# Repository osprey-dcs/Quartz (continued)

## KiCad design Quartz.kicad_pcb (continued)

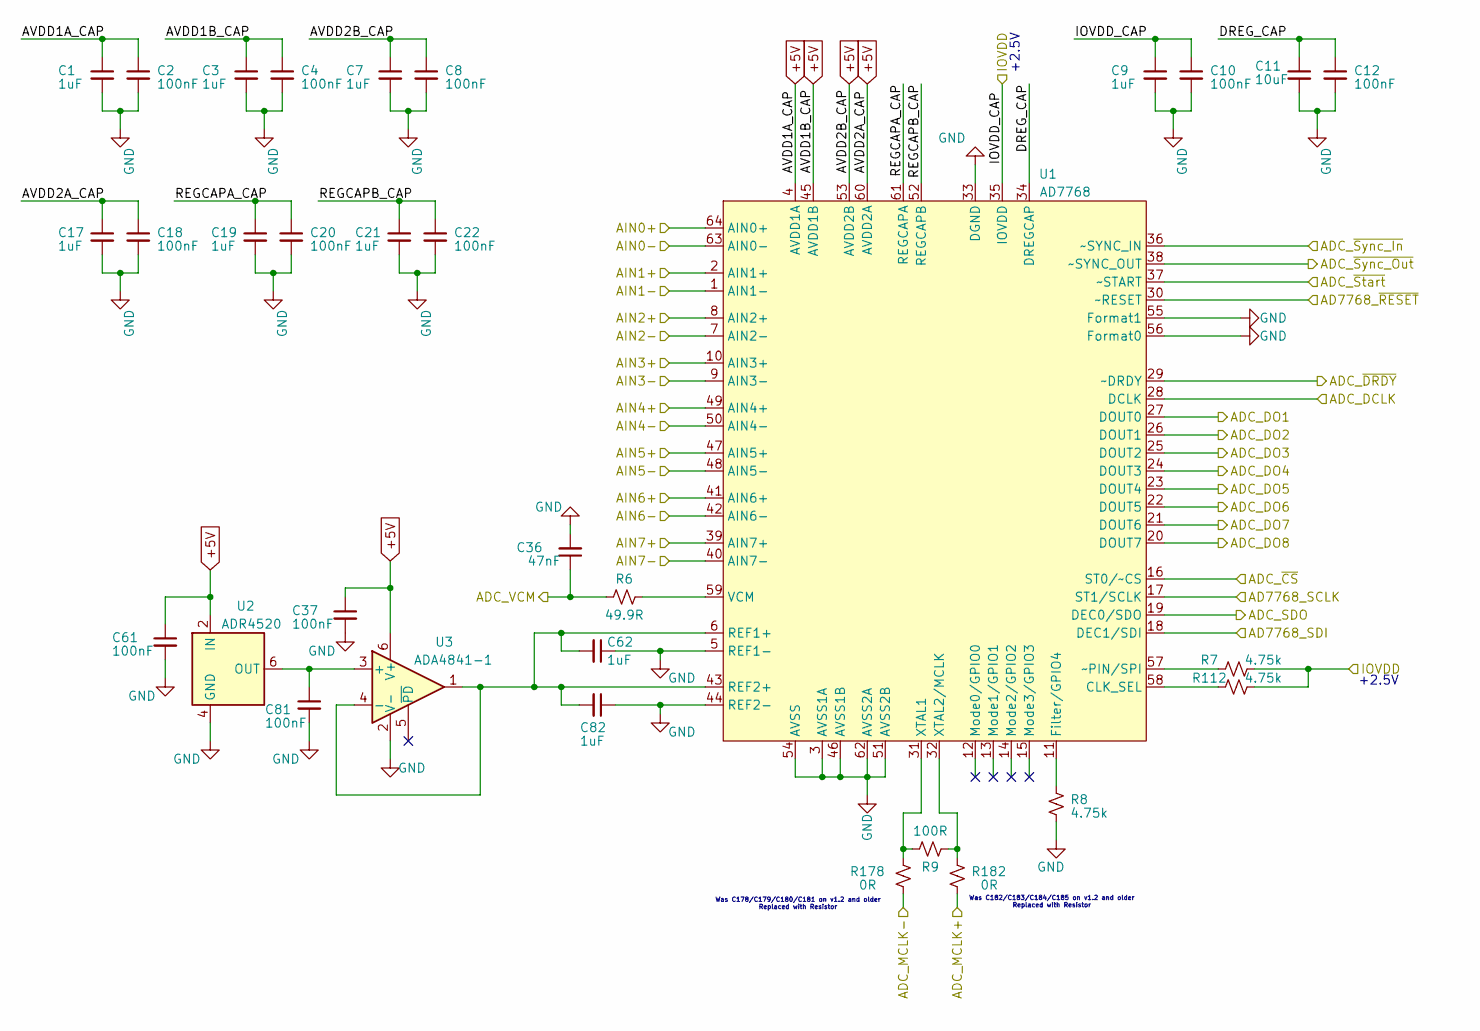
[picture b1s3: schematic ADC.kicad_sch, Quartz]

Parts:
C1, C3, C7, C9, C17, C19, C21, C62, C82: 1uF; C_0402_1005Metric; MPN CL05X105KP5NNNC
C2, C4, C8, C10, C12, C18, C20, C22, C37, C61, C81: 100nF; C_0402_1005Metric; MPN CL05A104KA5NNNC
C11: 10uF; C_0805_2012Metric; MPN CL21A106KOQNNNE
C36: 47nF; C_0402_1005Metric; MPN CGA2B3X7R1H473K050BB
R6: 49.9R; R_0402_1005Metric; MPN RC0402FR-0749R9L
R7, R8, R112: 4.75k; R_0402_1005Metric; MPN RC0402FR-074K75L
R9: 100R; R_0402_1005Metric; MPN RC0402FR-07100RL
R178, R182: 0R; R_0603_1608Metric; MPN ERJ-2GE0R00X
U1: AD7768; LQFP-64_10x10mm_P0.5mm; MPN AD7768BSTZ
U2: ADR4520; SOIC-8_3.9x4.9mm_P1.27mm; MPN ADR4520BRZ
U3: ADA4841-1; SOT-23-6; MPN ADA4841-1YRJZ-R2

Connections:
+5V: C1.1, C2.1, C3.1, C4.1, C7.1, C8.1, C17.1, C18.1, C37.1, C61.1, U1.4 (AVDD1A), U1.45 (AVDD1B), U1.53 (AVDD2B), U1.60 (AVDD2A), U2.2 (IN), U3.6 (V+); also elsewhere on the board
/ADC1/AIN0+: U1.64 (AIN0+); also elsewhere on the board
/ADC1/AIN0-: U1.63 (AIN0-); also elsewhere on the board
/ADC1/AIN1+: U1.2 (AIN1+); also elsewhere on the board
/ADC1/AIN1-: U1.1 (AIN1-); also elsewhere on the board
/ADC1/AIN2+: U1.8 (AIN2+); also elsewhere on the board
/ADC1/AIN2-: U1.7 (AIN2-); also elsewhere on the board
/ADC1/AIN3+: U1.10 (AIN3+); also elsewhere on the board
/ADC1/AIN3-: U1.9 (AIN3-); also elsewhere on the board
/ADC1/AIN4+: U1.49 (AIN4+); also elsewhere on the board
/ADC1/AIN4-: U1.50 (AIN4-); also elsewhere on the board
/ADC1/AIN5+: U1.47 (AIN5+); also elsewhere on the board
/ADC1/AIN5-: U1.48 (AIN5-); also elsewhere on the board
/ADC1/AIN6+: U1.41 (AIN6+); also elsewhere on the board
/ADC1/AIN6-: U1.42 (AIN6-); also elsewhere on the board
/ADC1/AIN7+: U1.39 (AIN7+); also elsewhere on the board
/ADC1/AIN7-: U1.40 (AIN7-); also elsewhere on the board
/ADC1/DREG_CAP: C11.1, C12.1, U1.34 (DREGCAP)
/ADC1/REGCAPA_CAP: C19.1, C20.1, U1.61 (REGCAPA)
/ADC1/REGCAPB_CAP: C21.1, C22.1, U1.52 (REGCAPB)
/ADC_VCM1: C36.1, R6.1; also elsewhere on the board
AD7768_SCLK: U1.17 (ST1/SCLK); also elsewhere on the board
AD7768_SDI: U1.18 (DEC1/SDI); also elsewhere on the board
AD7768_SYNC: U1.36 (~SYNC_IN), U1.38 (~SYNC_OUT); also elsewhere on the board
AD7768_~RESET: U1.30 (~RESET); also elsewhere on the board
AD7768_~Start: U1.37 (~START); also elsewhere on the board
ADC1_DCLK: U1.28 (DCLK); also elsewhere on the board
ADC1_DO1: U1.27 (DOUT0); also elsewhere on the board
ADC1_DO2: U1.26 (DOUT1); also elsewhere on the board
ADC1_DO3: U1.25 (DOUT2); also elsewhere on the board
ADC1_DO4: U1.24 (DOUT3); also elsewhere on the board
ADC1_DO5: U1.23 (DOUT4); also elsewhere on the board
ADC1_DO6: U1.22 (DOUT5); also elsewhere on the board
ADC1_DO7: U1.21 (DOUT6); also elsewhere on the board
ADC1_DO8: U1.20 (DOUT7); also elsewhere on the board
ADC1_MCLK+: R182.2; also elsewhere on the board
ADC1_MCLK-: R178.2; also elsewhere on the board
ADC1_SDO: U1.19 (DEC0/SDO); also elsewhere on the board
ADC1_~CS: U1.16 (ST0/~CS); also elsewhere on the board
ADC1_~DRDY: U1.29 (~DRDY); also elsewhere on the board
GND: C1.2, C2.2, C3.2, C4.2, C7.2, C8.2, C9.2, C10.2, C11.2, C12.2, C17.2, C18.2, C19.2, C20.2, C21.2, C22.2, C36.2, C37.2, C61.2, C62.1, C81.2, C82.1, R8.2, U1.3 (AVSS1A), U1.5 (REF1-), U1.33 (DGND), U1.44 (REF2-), U1.46 (AVSS1B), U1.51 (AVSS2B), U1.54 (AVSS), U1.55 (Format1), U1.56 (Format0), U1.62 (AVSS2A), U2.4 (GND), U3.2 (V-); also elsewhere on the board
unnamed: R112.2, U1.58 (CLK_SEL)
unnamed: R8.1, U1.11 (Filter/GPIO4)
unnamed: C62.2, C82.2, U1.6 (REF1+), U1.43 (REF2+), U3.1, U3.4 (-)
unnamed: R6.2, U1.59 (VCM)
unnamed: R9.1, R178.1, U1.31 (XTAL1)
unnamed: R9.2, R182.1, U1.32 (XTAL2/MCLK)
unnamed: R7.2, U1.57 (~PIN/SPI)
unnamed: C81.1, U2.6 (OUT), U3.3 (+)
P1_2P5V: C9.1, C10.1, R7.1, R112.1, U1.35 (IOVDD); also elsewhere on the board

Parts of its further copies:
C5, C13, C15, C23, C24, C27, C29, C31, C34, C38, C40, C42, C47, C50, C53, C55, C57, C59, C63, C68, C71, C73, C75, C77, C79, C86, C88: 1uF; C_0402_1005Metric; MPN CL05X105KP5NNNC
C6, C14, C16, C25, C26, C28, C30, C33, C35, C39, C41, C43, C45, C46, C48, C49, C52, C54, C56, C58, C60, C64, C66, C67, C70, C72, C74, C76, C78, C80, C84, C85, C87: 100nF; C_0402_1005Metric; MPN CL05A104KA5NNNC
C32, C51, C69: 10uF; C_0805_2012Metric; MPN CL21A106KOQNNNE
C44, C65, C83: 47nF; C_0402_1005Metric; MPN CGA2B3X7R1H473K050BB
R12, R18, R24: 49.9R; R_0402_1005Metric; MPN RC0402FR-0749R9L
R13, R14, R19, R20, R25, R26, R113, R114, R115: 4.75k; R_0402_1005Metric; MPN RC0402FR-074K75L
R15, R21, R27: 100R; R_0402_1005Metric; MPN RC0402FR-07100RL
R179, R180, R181, R183, R184, R185: 0R; R_0603_1608Metric; MPN ERJ-2GE0R00X
U4, U7, U10: AD7768; LQFP-64_10x10mm_P0.5mm; MPN AD7768BSTZ
U5, U8, U11: ADR4520; SOIC-8_3.9x4.9mm_P1.27mm; MPN ADR4520BRZ
U6, U9, U12: ADA4841-1; SOT-23-6; MPN ADA4841-1YRJZ-R2

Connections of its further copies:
+5V: C5.1, C6.1, C13.1, C14.1, C15.1, C16.1, C23.1, C24.1, C25.1, C26.1, C27.1, C28.1, C31.1, C34.1, C35.1, C38.1, C39.1, C45.1, C46.1, C49.1, C53.1, C54.1, C55.1, C56.1, C66.1, C67.1, C71.1, C72.1, C84.1, C85.1, U4.4 (AVDD1A), U4.45 (AVDD1B), U4.53 (AVDD2B), U4.60 (AVDD2A), U5.2 (IN), U6.6 (V+), U7.4 (AVDD1A), U7.45 (AVDD1B), U7.53 (AVDD2B), U7.60 (AVDD2A), U8.2 (IN), U9.6 (V+), U10.4 (AVDD1A), U10.45 (AVDD1B), U10.53 (AVDD2B), U10.60 (AVDD2A), U11.2 (IN), U12.6 (V+); also elsewhere on the board
/ADC2/ADC_~Start: U4.37 (~START); also elsewhere on the board
/ADC2/ADC_~Sync_Out: U4.38 (~SYNC_OUT)
/ADC2/AIN0+: U4.64 (AIN0+); also elsewhere on the board
/ADC2/AIN0-: U4.63 (AIN0-); also elsewhere on the board
/ADC2/AIN1+: U4.2 (AIN1+); also elsewhere on the board
/ADC2/AIN1-: U4.1 (AIN1-); also elsewhere on the board
/ADC2/AIN2+: U4.8 (AIN2+); also elsewhere on the board
/ADC2/AIN2-: U4.7 (AIN2-); also elsewhere on the board
/ADC2/AIN3+: U4.10 (AIN3+); also elsewhere on the board
/ADC2/AIN3-: U4.9 (AIN3-); also elsewhere on the board
/ADC2/AIN4+: U4.49 (AIN4+); also elsewhere on the board
/ADC2/AIN4-: U4.50 (AIN4-); also elsewhere on the board
/ADC2/AIN5+: U4.47 (AIN5+); also elsewhere on the board
/ADC2/AIN5-: U4.48 (AIN5-); also elsewhere on the board
/ADC2/AIN6+: U4.41 (AIN6+); also elsewhere on the board
/ADC2/AIN6-: U4.42 (AIN6-); also elsewhere on the board
/ADC2/AIN7+: U4.39 (AIN7+); also elsewhere on the board
/ADC2/AIN7-: U4.40 (AIN7-); also elsewhere on the board
/ADC2/DREG_CAP: C32.1, C33.1, U4.34 (DREGCAP)
/ADC2/REGCAPA_CAP: C40.1, C41.1, U4.61 (REGCAPA)
/ADC2/REGCAPB_CAP: C42.1, C43.1, U4.52 (REGCAPB)
/ADC3/ADC_~Start: U7.37 (~START); also elsewhere on the board
/ADC3/ADC_~Sync_Out: U7.38 (~SYNC_OUT)
/ADC3/AIN0+: U7.64 (AIN0+); also elsewhere on the board
/ADC3/AIN0-: U7.63 (AIN0-); also elsewhere on the board
/ADC3/AIN1+: U7.2 (AIN1+); also elsewhere on the board
/ADC3/AIN1-: U7.1 (AIN1-); also elsewhere on the board
/ADC3/AIN2+: U7.8 (AIN2+); also elsewhere on the board
/ADC3/AIN2-: U7.7 (AIN2-); also elsewhere on the board
/ADC3/AIN3+: U7.10 (AIN3+); also elsewhere on the board
/ADC3/AIN3-: U7.9 (AIN3-); also elsewhere on the board
/ADC3/AIN4+: U7.49 (AIN4+); also elsewhere on the board
/ADC3/AIN4-: U7.50 (AIN4-); also elsewhere on the board
/ADC3/AIN5+: U7.47 (AIN5+); also elsewhere on the board
/ADC3/AIN5-: U7.48 (AIN5-); also elsewhere on the board
/ADC3/AIN6+: U7.41 (AIN6+); also elsewhere on the board
/ADC3/AIN6-: U7.42 (AIN6-); also elsewhere on the board
/ADC3/AIN7+: U7.39 (AIN7+); also elsewhere on the board
/ADC3/AIN7-: U7.40 (AIN7-); also elsewhere on the board
/ADC3/DREG_CAP: C51.1, C52.1, U7.34 (DREGCAP)
/ADC3/REGCAPA_CAP: C57.1, C58.1, U7.61 (REGCAPA)
/ADC3/REGCAPB_CAP: C63.1, C64.1, U7.52 (REGCAPB)
/ADC4/ADC_~Start: U10.37 (~START); also elsewhere on the board
/ADC4/ADC_~Sync_Out: U10.38 (~SYNC_OUT)
/ADC4/AIN0+: U10.64 (AIN0+); also elsewhere on the board
/ADC4/AIN0-: U10.63 (AIN0-); also elsewhere on the board
/ADC4/AIN1+: U10.2 (AIN1+); also elsewhere on the board
/ADC4/AIN1-: U10.1 (AIN1-); also elsewhere on the board
/ADC4/AIN2+: U10.8 (AIN2+); also elsewhere on the board
/ADC4/AIN2-: U10.7 (AIN2-); also elsewhere on the board
/ADC4/AIN3+: U10.10 (AIN3+); also elsewhere on the board
/ADC4/AIN3-: U10.9 (AIN3-); also elsewhere on the board
/ADC4/AIN4+: U10.49 (AIN4+); also elsewhere on the board
/ADC4/AIN4-: U10.50 (AIN4-); also elsewhere on the board
/ADC4/AIN5+: U10.47 (AIN5+); also elsewhere on the board
/ADC4/AIN5-: U10.48 (AIN5-); also elsewhere on the board
/ADC4/AIN6+: U10.41 (AIN6+); also elsewhere on the board
/ADC4/AIN6-: U10.42 (AIN6-); also elsewhere on the board
/ADC4/AIN7+: U10.39 (AIN7+); also elsewhere on the board
/ADC4/AIN7-: U10.40 (AIN7-); also elsewhere on the board
/ADC4/DREG_CAP: C69.1, C70.1, U10.34 (DREGCAP)
/ADC4/REGCAPA_CAP: C73.1, C78.1, U10.61 (REGCAPA)
/ADC4/REGCAPB_CAP: C79.1, C80.1, U10.52 (REGCAPB)
/ADC_VCM2: C44.1, R12.1; also elsewhere on the board
/ADC_VCM3: C65.1, R18.1; also elsewhere on the board
/ADC_VCM4: C83.1, R24.1; also elsewhere on the board
AD7768_SCLK: U4.17 (ST1/SCLK), U7.17 (ST1/SCLK), U10.17 (ST1/SCLK); also elsewhere on the board
AD7768_SDI: U4.18 (DEC1/SDI), U7.18 (DEC1/SDI), U10.18 (DEC1/SDI); also elsewhere on the board
AD7768_SYNC: U4.36 (~SYNC_IN), U7.36 (~SYNC_IN), U10.36 (~SYNC_IN); also elsewhere on the board
AD7768_~RESET: U4.30 (~RESET), U7.30 (~RESET), U10.30 (~RESET); also elsewhere on the board
ADC2_DCLK: U4.28 (DCLK); also elsewhere on the board
ADC2_DO1: U4.27 (DOUT0); also elsewhere on the board
ADC2_DO2: U4.26 (DOUT1); also elsewhere on the board
ADC2_DO3: U4.25 (DOUT2); also elsewhere on the board
ADC2_DO4: U4.24 (DOUT3); also elsewhere on the board
ADC2_DO5: U4.23 (DOUT4); also elsewhere on the board
ADC2_DO6: U4.22 (DOUT5); also elsewhere on the board
ADC2_DO7: U4.21 (DOUT6); also elsewhere on the board
ADC2_DO8: U4.20 (DOUT7); also elsewhere on the board
ADC2_MCLK+: R183.2; also elsewhere on the board
ADC2_MCLK-: R179.2; also elsewhere on the board
ADC2_SDO: U4.19 (DEC0/SDO); also elsewhere on the board
ADC2_~CS: U4.16 (ST0/~CS); also elsewhere on the board
ADC2_~DRDY: U4.29 (~DRDY); also elsewhere on the board
ADC3_DCLK: U7.28 (DCLK); also elsewhere on the board
ADC3_DO1: U7.27 (DOUT0); also elsewhere on the board
ADC3_DO2: U7.26 (DOUT1); also elsewhere on the board
ADC3_DO3: U7.25 (DOUT2); also elsewhere on the board
ADC3_DO4: U7.24 (DOUT3); also elsewhere on the board
ADC3_DO5: U7.23 (DOUT4); also elsewhere on the board
ADC3_DO6: U7.22 (DOUT5); also elsewhere on the board
ADC3_DO7: U7.21 (DOUT6); also elsewhere on the board
ADC3_DO8: U7.20 (DOUT7); also elsewhere on the board
ADC3_MCLK+: R184.2; also elsewhere on the board
ADC3_MCLK-: R180.2; also elsewhere on the board
ADC3_SDO: U7.19 (DEC0/SDO); also elsewhere on the board
ADC3_~CS: U7.16 (ST0/~CS); also elsewhere on the board
ADC3_~DRDY: U7.29 (~DRDY); also elsewhere on the board
ADC4_DCLK: U10.28 (DCLK); also elsewhere on the board
ADC4_DO1: U10.27 (DOUT0); also elsewhere on the board
ADC4_DO2: U10.26 (DOUT1); also elsewhere on the board
ADC4_DO3: U10.25 (DOUT2); also elsewhere on the board
ADC4_DO4: U10.24 (DOUT3); also elsewhere on the board
ADC4_DO5: U10.23 (DOUT4); also elsewhere on the board
ADC4_DO6: U10.22 (DOUT5); also elsewhere on the board
ADC4_DO7: U10.21 (DOUT6); also elsewhere on the board
ADC4_DO8: U10.20 (DOUT7); also elsewhere on the board
ADC4_MCLK+: R185.2; also elsewhere on the board
ADC4_MCLK-: R181.2; also elsewhere on the board
ADC4_SDO: U10.19 (DEC0/SDO); also elsewhere on the board
ADC4_~CS: U10.16 (ST0/~CS); also elsewhere on the board
ADC4_~DRDY: U10.29 (~DRDY); also elsewhere on the board
GND: C5.2, C6.2, C13.2, C14.2, C15.2, C16.2, C23.2, C24.2, C25.2, C26.2, C27.2, C28.2, C29.2, C30.2, C31.2, C32.2, C33.2, C34.2, C35.2, C38.2, C39.2, C40.2, C41.2, C42.2, C43.2, C44.2, C45.2, C46.2, C47.2, C48.2, C49.2, C50.1, C51.2, C52.2, C53.2, C54.2, C55.2, C56.2, C57.2, C58.2, C59.2, C60.2, C63.2, C64.2, C65.2, C66.2, C67.2, C68.1, C69.2, C70.2, C71.2, C72.2, C73.2, C74.2, C75.1, C76.2, C77.1, C78.2, C79.2, C80.2, C83.2, C84.2, C85.2, C86.1, C87.2, C88.1, R14.2, R20.2, R26.2, U4.3 (AVSS1A), U4.5 (REF1-), U4.33 (DGND), U4.44 (REF2-), U4.46 (AVSS1B), U4.51 (AVSS2B), U4.54 (AVSS), U4.55 (Format1), U4.56 (Format0), U4.62 (AVSS2A), U5.4 (GND), U6.2 (V-), U7.3 (AVSS1A), U7.5 (REF1-), U7.33 (DGND), U7.44 (REF2-), U7.46 (AVSS1B), U7.51 (AVSS2B), U7.54 (AVSS), U7.55 (Format1), U7.56 (Format0), U7.62 (AVSS2A), U8.4 (GND), U9.2 (V-), U10.3 (AVSS1A), U10.5 (REF1-), U10.33 (DGND), U10.44 (REF2-), U10.46 (AVSS1B), U10.51 (AVSS2B), U10.54 (AVSS), U10.55 (Format1), U10.56 (Format0), U10.62 (AVSS2A), U11.4 (GND), U12.2 (V-); also elsewhere on the board
unnamed: R113.2, U4.58 (CLK_SEL)
unnamed: R14.1, U4.11 (Filter/GPIO4)
unnamed: C50.2, C75.2, U4.6 (REF1+), U4.43 (REF2+), U6.1, U6.4 (-)
unnamed: R12.2, U4.59 (VCM)
unnamed: R15.1, R179.1, U4.31 (XTAL1)
unnamed: R15.2, R183.1, U4.32 (XTAL2/MCLK)
unnamed: R13.2, U4.57 (~PIN/SPI)
unnamed: C74.1, U5.6 (OUT), U6.3 (+)
unnamed: R114.2, U7.58 (CLK_SEL)
unnamed: R20.1, U7.11 (Filter/GPIO4)
unnamed: C68.2, C77.2, U7.6 (REF1+), U7.43 (REF2+), U9.1, U9.4 (-)
unnamed: R18.2, U7.59 (VCM)
unnamed: R21.1, R180.1, U7.31 (XTAL1)
unnamed: R21.2, R184.1, U7.32 (XTAL2/MCLK)
unnamed: R19.2, U7.57 (~PIN/SPI)
unnamed: C76.1, U8.6 (OUT), U9.3 (+)
unnamed: R115.2, U10.58 (CLK_SEL)
unnamed: R26.1, U10.11 (Filter/GPIO4)
unnamed: C86.2, C88.2, U10.6 (REF1+), U10.43 (REF2+), U12.1, U12.4 (-)
unnamed: R24.2, U10.59 (VCM)
unnamed: R27.1, R181.1, U10.31 (XTAL1)
unnamed: R27.2, R185.1, U10.32 (XTAL2/MCLK)
unnamed: R25.2, U10.57 (~PIN/SPI)
unnamed: C87.1, U11.6 (OUT), U12.3 (+)
P1_2P5V: C29.1, C30.1, R13.1, R113.1, U4.35 (IOVDD); also elsewhere on the board
P2_2P5V: C47.1, C48.1, C59.1, C60.1, R19.1, R25.1, R114.1, R115.1, U7.35 (IOVDD), U10.35 (IOVDD); also elsewhere on the board

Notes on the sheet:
+2.5V
Was C178/C179/C180/C181 on v1.2 and older Replaced with Resistor
Was C182/C183/C184/C185 on v1.2 and older Replaced with Resistor

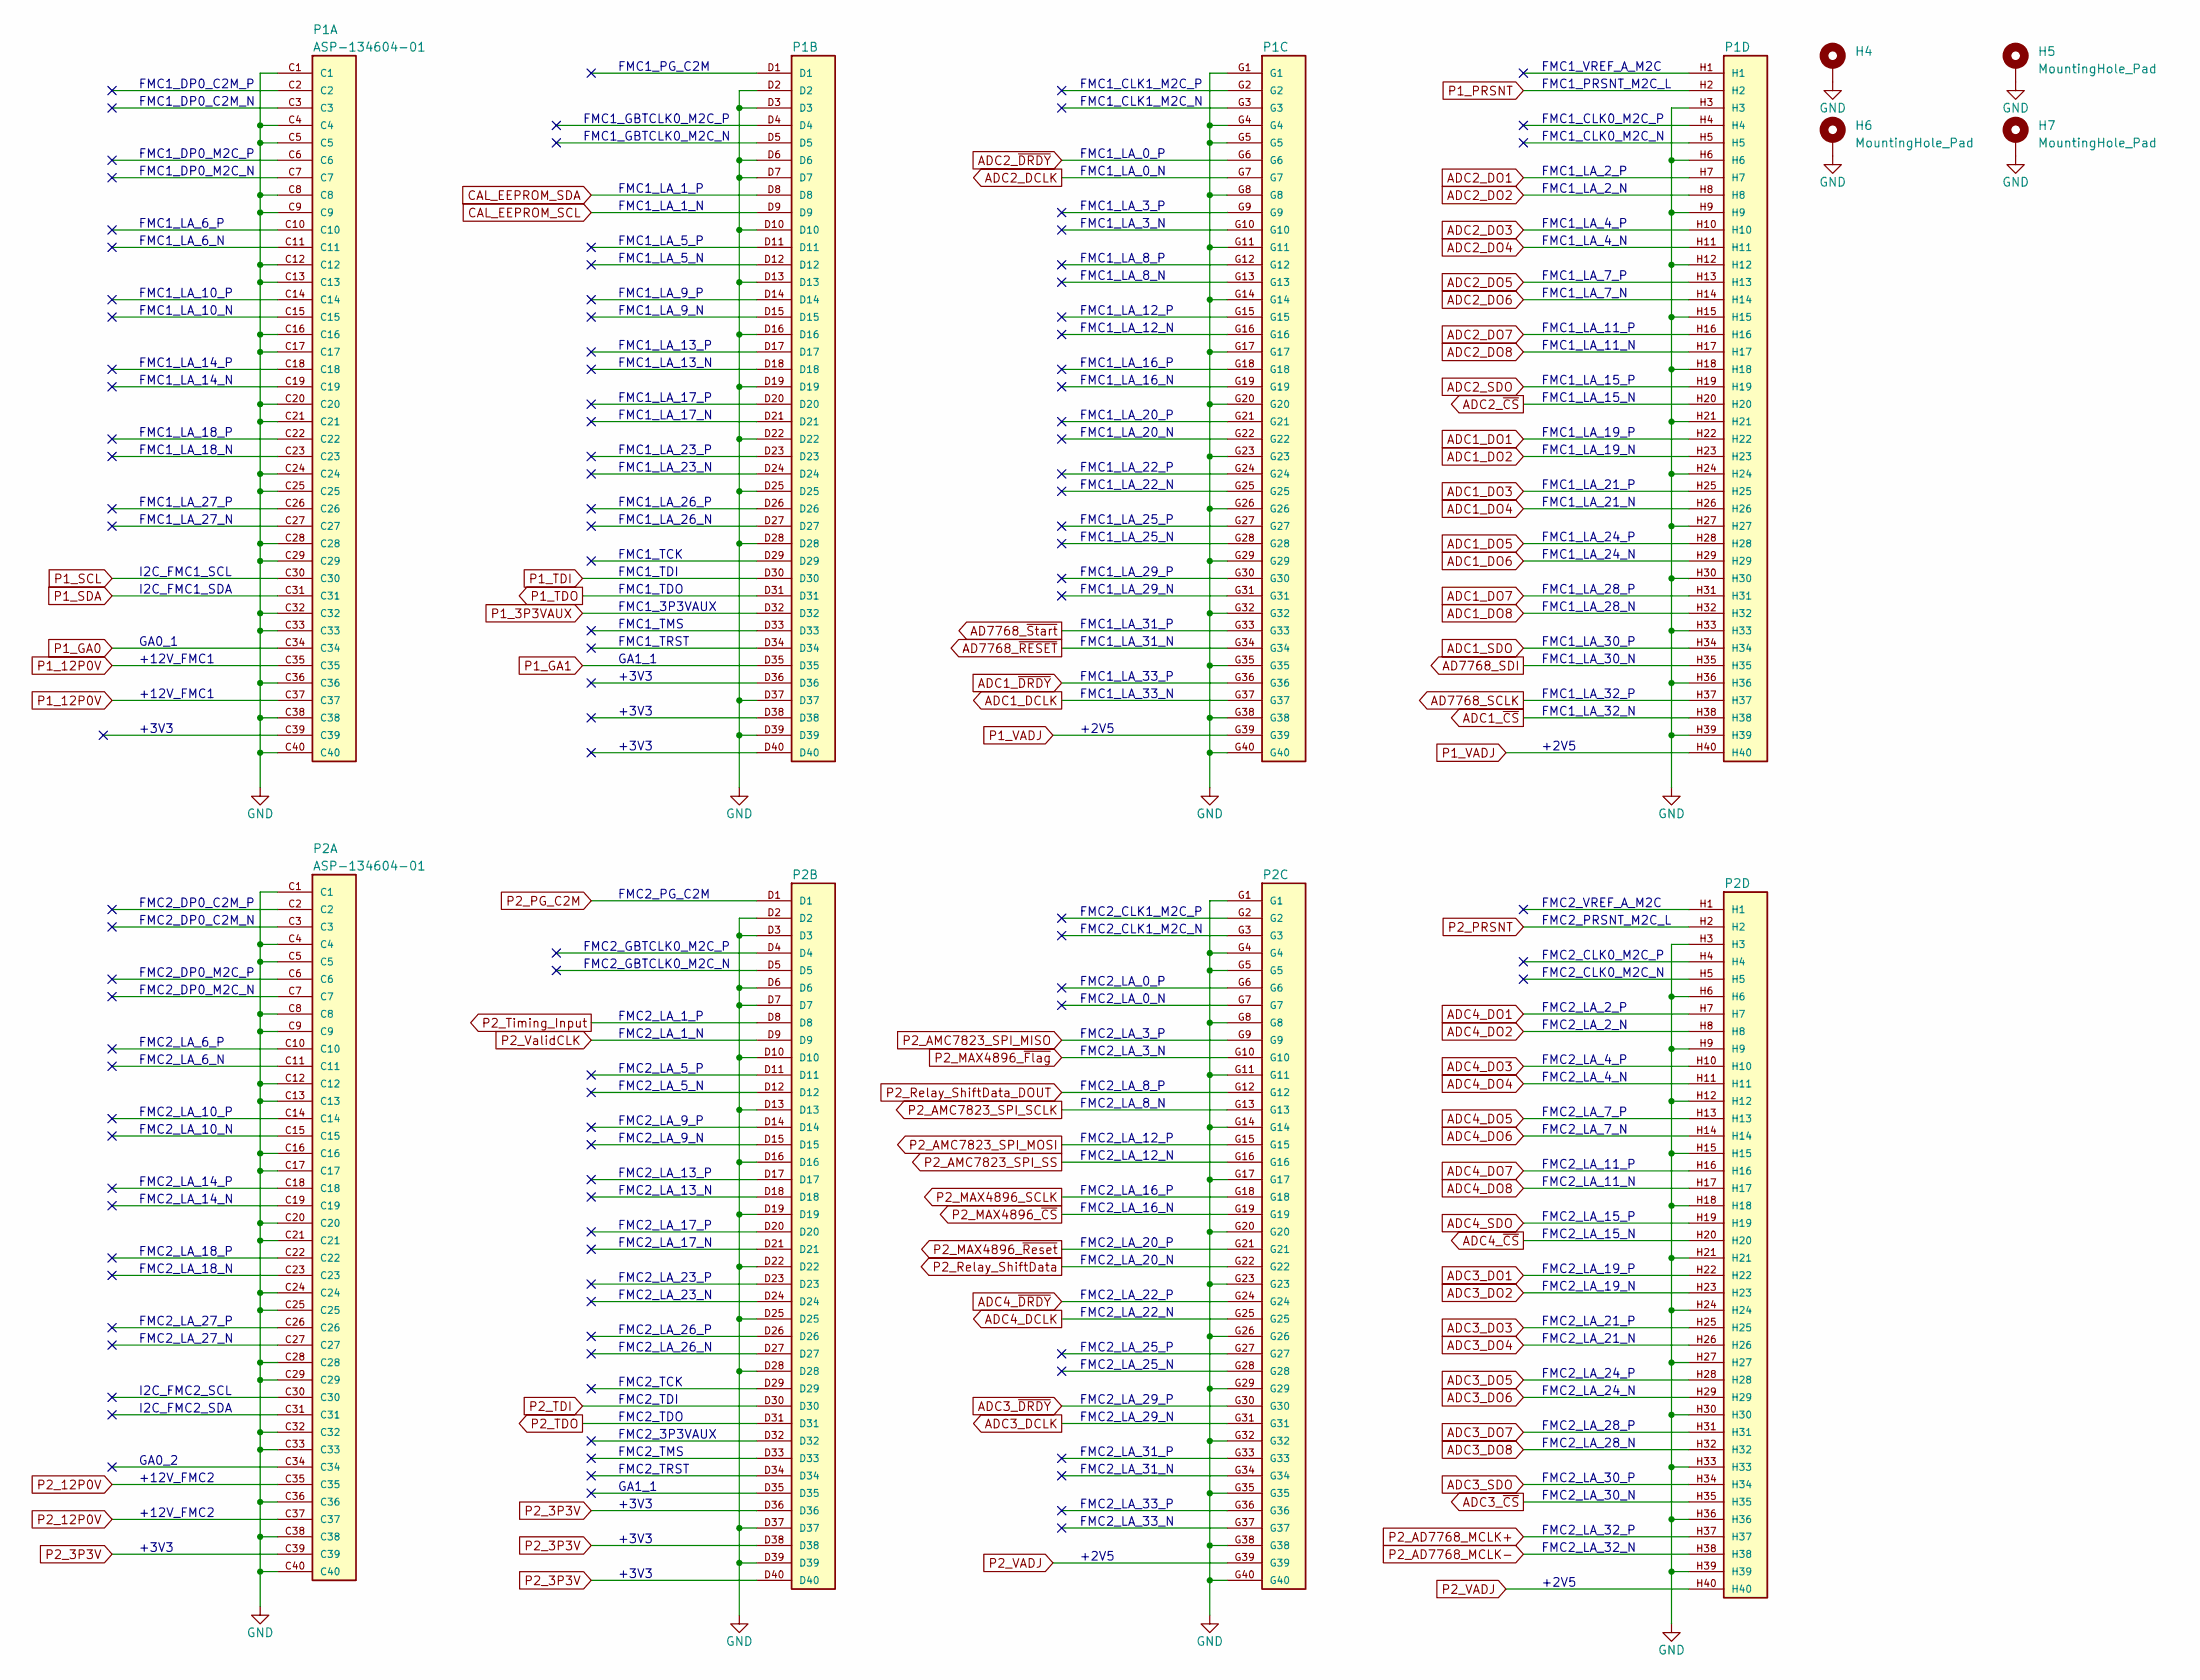
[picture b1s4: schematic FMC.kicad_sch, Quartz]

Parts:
H4, H5, H6, H7: MountingHole_Pad; Mounting Hole 3mm hole 5mm ring
P1, P2: ASP-134604-01; SAMTEC_ASP-134604-01; MPN ASP-134604-01

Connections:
AD7768_SCLK: P1.H37; also elsewhere on the board
AD7768_SDI: P1.H35; also elsewhere on the board
AD7768_~RESET: P1.G34; also elsewhere on the board
AD7768_~Start: P1.G33; also elsewhere on the board
ADC1_DCLK: P1.G37; also elsewhere on the board
ADC1_DO1: P1.H22; also elsewhere on the board
ADC1_DO2: P1.H23; also elsewhere on the board
ADC1_DO3: P1.H25; also elsewhere on the board
ADC1_DO4: P1.H26; also elsewhere on the board
ADC1_DO5: P1.H28; also elsewhere on the board
ADC1_DO6: P1.H29; also elsewhere on the board
ADC1_DO7: P1.H31; also elsewhere on the board
ADC1_DO8: P1.H32; also elsewhere on the board
ADC1_SDO: P1.H34; also elsewhere on the board
ADC1_~CS: P1.H38; also elsewhere on the board
ADC1_~DRDY: P1.G36; also elsewhere on the board
ADC2_DCLK: P1.G7; also elsewhere on the board
ADC2_DO1: P1.H7; also elsewhere on the board
ADC2_DO2: P1.H8; also elsewhere on the board
ADC2_DO3: P1.H10; also elsewhere on the board
ADC2_DO4: P1.H11; also elsewhere on the board
ADC2_DO5: P1.H13; also elsewhere on the board
ADC2_DO6: P1.H14; also elsewhere on the board
ADC2_DO7: P1.H16; also elsewhere on the board
ADC2_DO8: P1.H17; also elsewhere on the board
ADC2_SDO: P1.H19; also elsewhere on the board
ADC2_~CS: P1.H20; also elsewhere on the board
ADC2_~DRDY: P1.G6; also elsewhere on the board
ADC3_DCLK: P2.G31; also elsewhere on the board
ADC3_DO1: P2.H22; also elsewhere on the board
ADC3_DO2: P2.H23; also elsewhere on the board
ADC3_DO3: P2.H25; also elsewhere on the board
ADC3_DO4: P2.H26; also elsewhere on the board
ADC3_DO5: P2.H28; also elsewhere on the board
ADC3_DO6: P2.H29; also elsewhere on the board
ADC3_DO7: P2.H31; also elsewhere on the board
ADC3_DO8: P2.H32; also elsewhere on the board
ADC3_SDO: P2.H34; also elsewhere on the board
ADC3_~CS: P2.H35; also elsewhere on the board
ADC3_~DRDY: P2.G30; also elsewhere on the board
ADC4_DCLK: P2.G25; also elsewhere on the board
ADC4_DO1: P2.H7; also elsewhere on the board
ADC4_DO2: P2.H8; also elsewhere on the board
ADC4_DO3: P2.H10; also elsewhere on the board
ADC4_DO4: P2.H11; also elsewhere on the board
ADC4_DO5: P2.H13; also elsewhere on the board
ADC4_DO6: P2.H14; also elsewhere on the board
ADC4_DO7: P2.H16; also elsewhere on the board
ADC4_DO8: P2.H17; also elsewhere on the board
ADC4_SDO: P2.H19; also elsewhere on the board
ADC4_~CS: P2.H20; also elsewhere on the board
ADC4_~DRDY: P2.G24; also elsewhere on the board
CAL_EEPROM_SCL: P1.D9; also elsewhere on the board
CAL_EEPROM_SDA: P1.D8; also elsewhere on the board
GND: H4.1, H5.1, H6.1, H7.1, P1.C1, P1.C4, P1.C5, P1.C8, P1.C9, P1.C12, P1.C13, P1.C16, P1.C17, P1.C20, P1.C21, P1.C24, P1.C25, P1.C28, P1.C29, P1.C32, P1.C33, P1.C36, P1.C38, P1.C40, P1.D2, P1.D3, P1.D6, P1.D7, P1.D10, P1.D13, P1.D16, P1.D19, P1.D22, P1.D25, P1.D28, P1.D37, P1.D39, P1.G1, P1.G4, P1.G5, P1.G8, P1.G11, P1.G14, P1.G17, P1.G20, P1.G23, P1.G26, P1.G29, P1.G32, P1.G35, P1.G38, P1.G40, P1.H3, P1.H6, P1.H9, P1.H12, P1.H15, P1.H18, P1.H21, P1.H24, P1.H27, P1.H30, P1.H33, P1.H36, P1.H39, P2.C1, P2.C4, P2.C5, P2.C8, P2.C9, P2.C12, P2.C13, P2.C16, P2.C17, P2.C20, P2.C21, P2.C24, P2.C25, P2.C28, P2.C29, P2.C32, P2.C33, P2.C36, P2.C38, P2.C40, P2.D2, P2.D3, P2.D6, P2.D7, P2.D10, P2.D13, P2.D16, P2.D19, P2.D22, P2.D25, P2.D28, P2.D37, P2.D39, P2.G1, P2.G4, P2.G5, P2.G8, P2.G11, P2.G14, P2.G17, P2.G20, P2.G23, P2.G26, P2.G29, P2.G32, P2.G35, P2.G38, P2.G40, P2.H3, P2.H6, P2.H9, P2.H12, P2.H15, P2.H18, P2.H21, P2.H24, P2.H27, P2.H30, P2.H33, P2.H36, P2.H39; also elsewhere on the board
P1_3P3VAUX: P1.D32; also elsewhere on the board
P1_12P0V: P1.C35, P1.C37; also elsewhere on the board
P1_GA0: P1.C34; also elsewhere on the board
P1_GA1: P1.D35; also elsewhere on the board
P1_PRSNT: P1.H2; also elsewhere on the board
P1_SCL: P1.C30; also elsewhere on the board
P1_SDA: P1.C31; also elsewhere on the board
P1_TDI: P1.D30; also elsewhere on the board
P1_TDO: P1.D31; also elsewhere on the board
P1_VADJ: P1.G39, P1.H40; also elsewhere on the board
P2_3P3V: P2.C39, P2.D36, P2.D38, P2.D40; also elsewhere on the board
P2_12P0V: P2.C35, P2.C37; also elsewhere on the board
P2_AD7768_MCLK+: P2.H37; also elsewhere on the board
P2_AD7768_MCLK-: P2.H38; also elsewhere on the board
P2_AMC7823_SPI_MISO: P2.G9; also elsewhere on the board
P2_AMC7823_SPI_MOSI: P2.G15; also elsewhere on the board
P2_AMC7823_SPI_SCLK: P2.G13; also elsewhere on the board
P2_AMC7823_SPI_SS: P2.G16; also elsewhere on the board
P2_MAX4896_SCLK: P2.G18; also elsewhere on the board
P2_MAX4896_~CS: P2.G19; also elsewhere on the board
P2_MAX4896_~Flag: P2.G10; also elsewhere on the board
P2_MAX4896_~Reset: P2.G21; also elsewhere on the board
P2_PG_C2M: P2.D1; also elsewhere on the board
P2_PRSNT: P2.H2; also elsewhere on the board
P2_Relay_ShiftData: P2.G22; also elsewhere on the board
P2_Relay_ShiftData_DOUT: P2.G12; also elsewhere on the board
P2_TDI: P2.D30; also elsewhere on the board
P2_TDO: P2.D31; also elsewhere on the board
P2_Timing_Input: P2.D8; also elsewhere on the board
P2_VADJ: P2.G39, P2.H40; also elsewhere on the board
P2_ValidCLK: P2.D9; also elsewhere on the board

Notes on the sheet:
FMC1_DP0_C2M_N
FMC1_TDO
FMC2_LA_16_P
FMC2_LA_4_N
FMC2_DP0_M2C_P
FMC1_LA_25_P
FMC2_LA_19_N
FMC1_LA_20_P
FMC2_LA_30_P
FMC1_LA_26_N
FMC1_LA_12_P
FMC1_LA_29_N
FMC1_LA_5_P
FMC1_LA_24_P
FMC1_LA_33_N
FMC2_VREF_A_M2C
FMC2_LA_20_P
FMC1_LA_22_N
FMC2_DP0_M2C_N
FMC1_LA_1_P
+2V5
FMC2_LA_15_P
FMC2_LA_25_P
FMC2_LA_18_N
FMC2_LA_17_P
GA0_1
FMC2_LA_19_P
FMC1_LA_11_N
FMC2_LA_5_P
FMC2_LA_29_N
FMC1_LA_0_P
FMC2_LA_31_N
FMC2_LA_23_P
FMC1_LA_16_N
FMC2_LA_10_P
FMC1_LA_3_N
FMC2_LA_26_P
FMC1_LA_26_P
+3V3
FMC2_LA_14_P

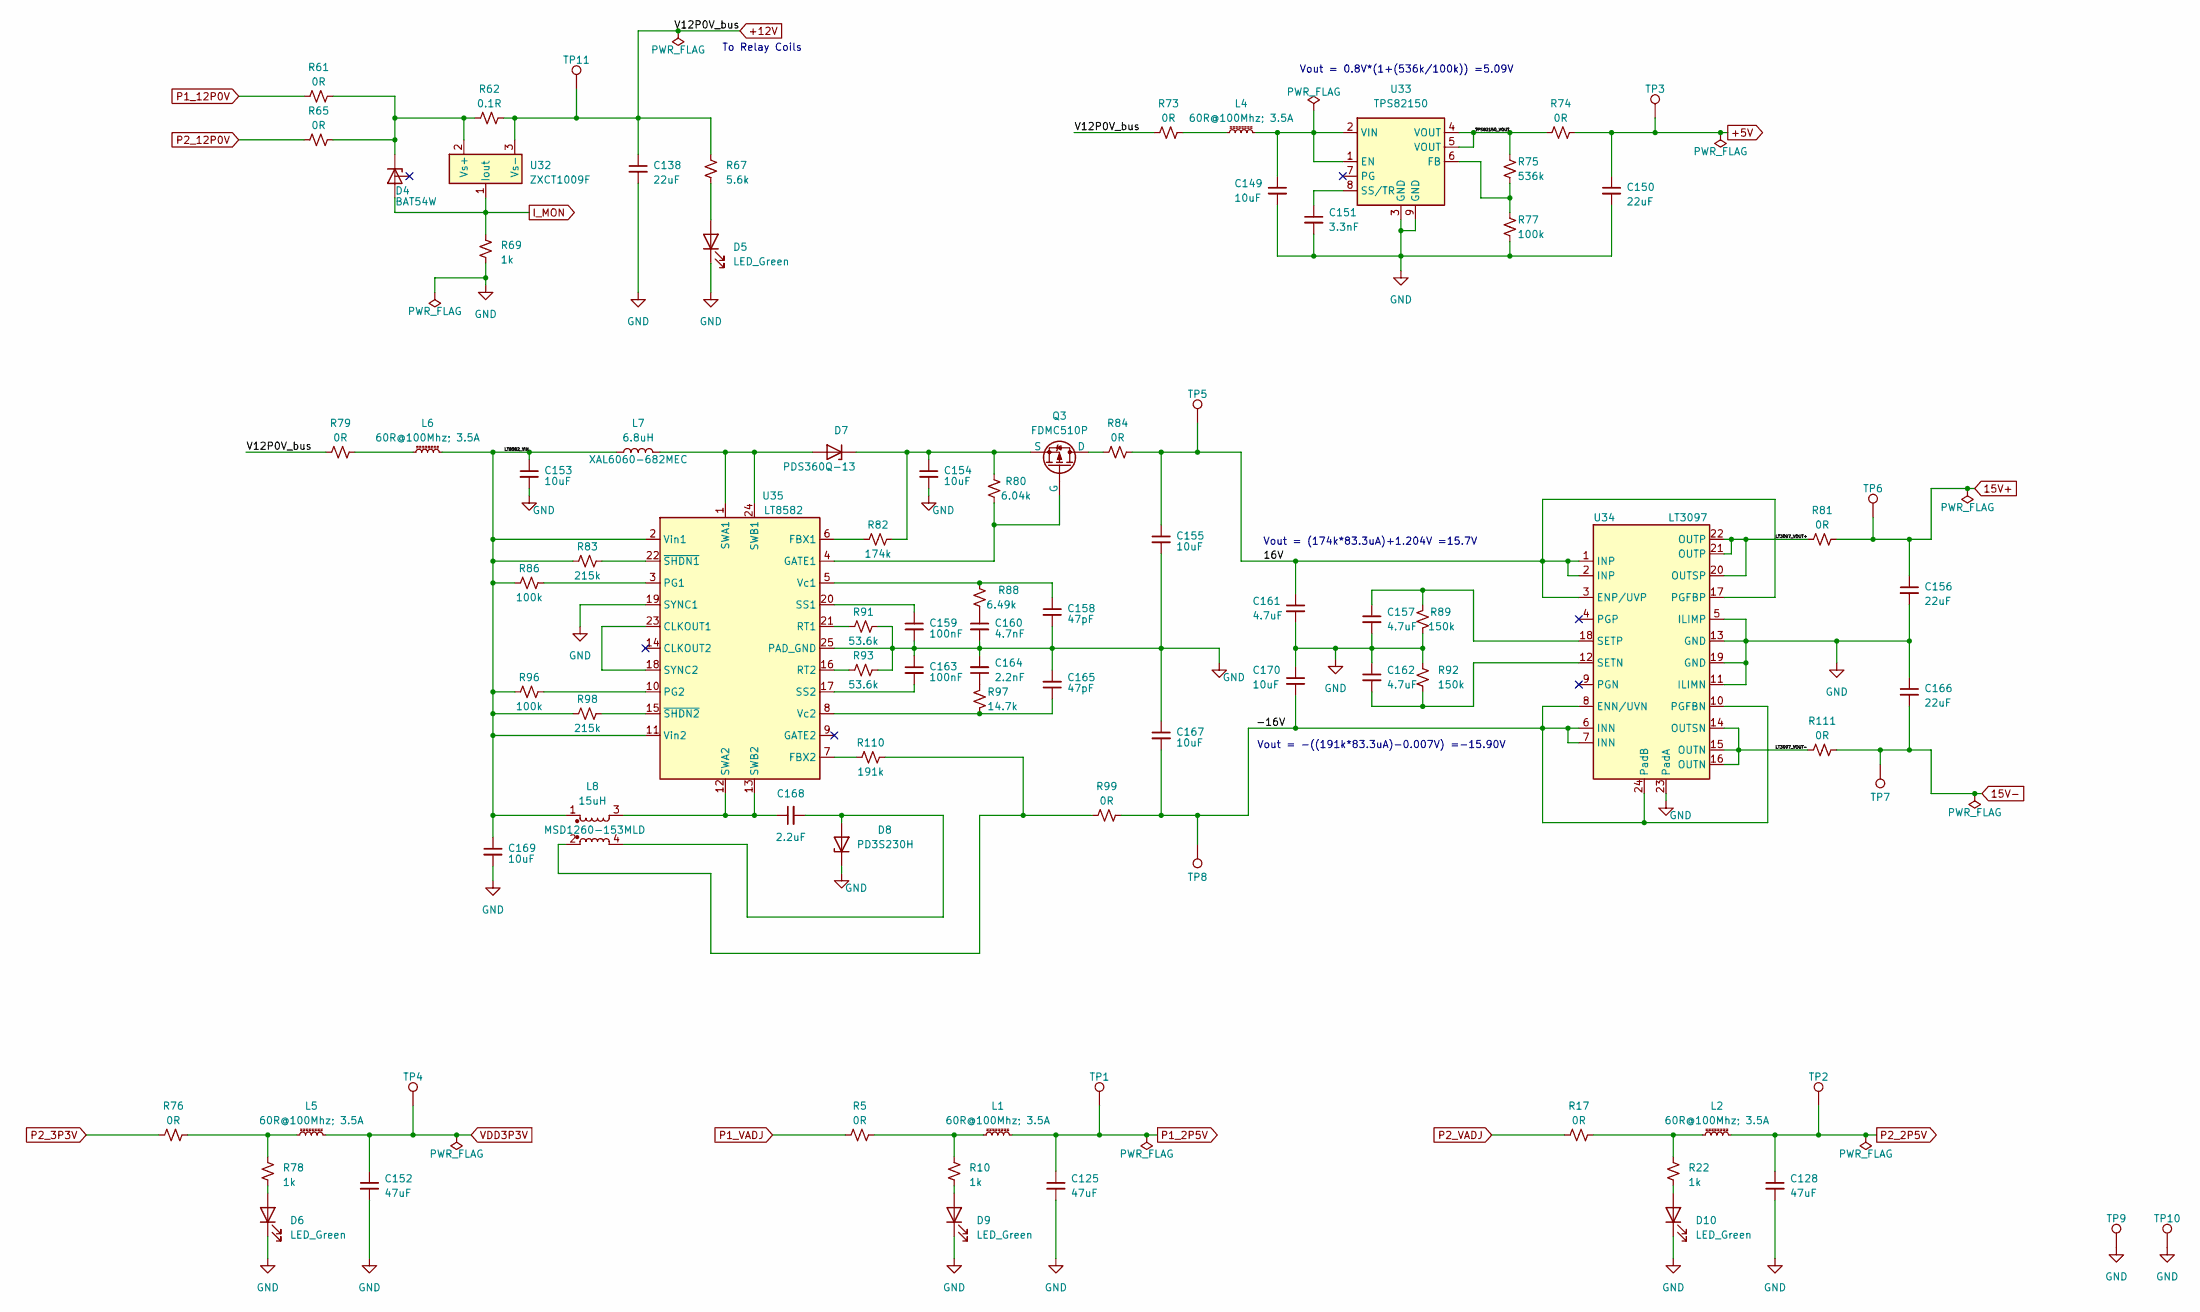
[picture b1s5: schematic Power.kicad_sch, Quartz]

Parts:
C125, C128, C152: 47uF; C_0805_2012Metric; MPN C2012X5R1A476M125AC
C138, C150, C156, C166: 22uF; C_0805_2012Metric; MPN GRT21BR61E226ME13L
C149, C153, C154, C155, C167, C169, C170: 10uF; C_0805_2012Metric; MPN GRM21BR61E106KA73L
C151: 3.3nF; C_0603_1608Metric; MPN GRM1885C1H332JA01D
C157, C161, C162: 4.7uF; C_0805_2012Metric; MPN TMK212AB7475KG-T
C158, C165: 47pF; C_0603_1608Metric; MPN GRM1885C1H470JA01D
C159, C163: 100nF; C_0402_1005Metric; MPN CL05A104KA5NNNC
C160: 4.7nF; C_0603_1608Metric; MPN CGA3E2C0G1H472J080AA
C164: 2.2nF; C_0603_1608Metric; MPN GCM1885C1H222JA16D
C168: 2.2uF; C_0805_2012Metric; MPN GRM21BR71E225KE11L
D4: BAT54W; SOT-323_SC-70; MPN BAT54W-7-F
D5, D6, D9, D10: LED_Green; LED_0603_1608Metric; MPN APT1608CGCK
D7: PDS360Q-13; D_PowerDI-5; MPN PDS360Q-13
D8: PD3S230H; D_SOD-323_HandSoldering; MPN PD3S230H-7
L1, L2, L4, L5, L6: 60R@100Mhz; 3.5A; L_0805_2012Metric; MPN BLM21PG600SN1D
L7: 6.8uH; IND_7345-WE-PD_WRE; MPN XAL6060-682MEC
L8: 15uH; MSD1260153MLD; MPN MSD1260-153MLD
Q3: FDMC510P; MLP8_3P3X3P3_ONS-M; MPN FDMC510P
R5, R17, R73, R74, R76, R79, R81, R84, R99, R111: 0R; R_0603_1608Metric; MPN ERJ-3GEY0R00V
R10, R22, R78: 1k; R_0603_1608Metric; MPN RC0603FR-071KL
R61, R65: 0R; R_0805_2012Metric; MPN ERJ-6GEY0R00V
R62: 0.1R; R_1206_3216Metric; MPN ERJ-8BWFR100V
R67: 5.6k; R_0603_1608Metric; MPN RC0603FR-075K6L
R69: 1k; R_0805_2012Metric; MPN RC0805FR-071KL
R75: 536k; R_0603_1608Metric; MPN RC0603FR-07536KL
R77: 100k; R_0603_1608Metric; MPN RC0603FR-07100KL
R80: 6.04k; R_0603_1608Metric; MPN RC0603FR-076K04L
R82: 174k; R_0603_1608Metric; MPN RC0603FR-07174KL
R83, R98: 215k; R_0402_1005Metric; MPN RC0402FR-07215KL
R86, R96: 100k; R_0402_1005Metric; MPN RC0402FR-07100KL
R88: 6.49k; R_0603_1608Metric; MPN RC0603FR-076K49L
R89, R92: 150k; R_0603_1608Metric; MPN RC0603FR-07150KL
R91, R93: 53.6k; R_0402_1005Metric; MPN RC0402FR-0753K6L
R97: 14.7k; R_0603_1608Metric; MPN RC0603FR-0714K7L
R110: 191k; R_0603_1608Metric; MPN RC0603FR-07191KL
TP1, TP2, TP3, TP4, TP5, TP6, TP7, TP8, TP11: TestPoint_Loop_D1.80mm_Drill1.0mm_Beaded; MPN 5000
TP9, TP10: TestPoint_Loop_D1.80mm_Drill1.0mm_Beaded; MPN 5001
U32: ZXCT1009F; SOT-23-PinRotate; MPN ZXCT1009FTA
U33: TPS82150; SIL0008D_SMD; MPN TPS82150SILR
U34: LT3097; 05-08-7071_ADI-M; MPN LT3097ADJC#PBF
U35: LT8582; DFN-24-1EP_4x7mm_P0.5mm_EP2.64x6.44mm; MPN LT8582EDKD#TRPBF

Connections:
15V+: C156.1, R81.2, TP6.1; also elsewhere on the board
15V-: C166.2, R111.2, TP7.1; also elsewhere on the board
+5V: C150.1, R74.2, TP3.1; also elsewhere on the board
+12V: C138.1, R62.2, R67.2, R73.1, R79.1, TP11.1, U32.3 (Vs-); also elsewhere on the board
/Power/16V: C155.1, C161.1, R84.2, TP5.1, U34.1 (INP), U34.2 (INP), U34.3 (ENP/UVP), U34.17 (PGFBP)
/Power/-16V: C167.2, C170.2, R99.2, TP8.1, U34.6 (INN), U34.7 (INN), U34.8 (ENN/UVN), U34.10 (PGFBN), U34.24 (PadB)
/Power/LT3097_VOUT+: R81.1, U34.20 (OUTSP), U34.21 (OUTP), U34.22 (OUTP)
/Power/LT3097_VOUT-: R111.1, U34.14 (OUTSN), U34.15 (OUTN), U34.16 (OUTN)
/Power/LT8582_VIN: C153.1, C169.1, L6.2, L7.1, L8.1, R83.1, R86.1, R96.1, R98.1, U35.2 (Vin1), U35.11 (Vin2)
/Power/TPS82150_VOUT: R74.1, R75.1, U33.4 (VOUT), U33.5 (VOUT)
GND: C125.2, C128.2, C138.2, C149.2, C150.2, C151.2, C152.2, C153.2, C154.2, C155.2, C156.2, C157.2, C158.2, C159.2, C160.2, C161.2, C162.1, C163.1, C164.2, C165.2, C166.1, C167.1, C169.2, C170.1, D5.1 (K), D6.1 (K), D8.1 (K), D9.1 (K), D10.1 (K), R69.2, R77.2, R89.2, R91.1, R92.1, R93.1, TP9.1, TP10.1, U33.3 (GND), U33.9 (GND), U34.5 (ILIMP), U34.11 (ILIMN), U34.13 (GND), U34.19 (GND), U34.23 (PadA), U35.19 (SYNC1), U35.25 (PAD_GND); also elsewhere on the board
I_MON: D4.1 (A), R69.1, U32.1 (Iout); also elsewhere on the board
unnamed: C160.1, R88.1
unnamed: C164.1, R97.1
unnamed: D4.3 (K), R61.2, R62.1, R65.2, U32.2 (Vs+)
unnamed: D5.2 (A), R67.1
unnamed: D6.2 (A), R78.1
unnamed: D7.2 (A), L7.2, U35.1 (SWA1), U35.24 (SWB1)
unnamed: C154.1, D7.1 (K), Q3.3 (S), R80.2, R82.2
unnamed: C168.2, D8.2 (A), L8.4
unnamed: D9.2 (A), R10.1
unnamed: D10.2 (A), R22.1
unnamed: L1.1, R5.2, R10.2
unnamed: L2.1, R17.2, R22.2
unnamed: L4.1, R73.2
unnamed: L5.1, R76.2, R78.2
unnamed: L6.1, R79.2
unnamed: L8.2, R99.1, R110.2
unnamed: Q3.1 (D), R84.1
unnamed: Q3.2 (G), R80.1, U35.4 (GATE1)
unnamed: C149.1, L4.2, U33.1 (EN), U33.2 (VIN)
unnamed: R75.2, R77.1, U33.6 (FB)
unnamed: C151.1, U33.8 (SS/TR)
unnamed: C162.2, R92.2, U34.12 (SETN)
unnamed: C157.1, R89.1, U34.18 (SETP)
unnamed: U35.18 (SYNC2), U35.23 (CLKOUT1)
unnamed: R82.1, U35.6 (FBX1)
unnamed: R110.1, U35.7 (FBX2)
unnamed: R86.2, U35.3 (PG1)
unnamed: R96.2, U35.10 (PG2)
unnamed: R91.2, U35.21 (RT1)
unnamed: R93.2, U35.16 (RT2)
unnamed: C159.1, U35.20 (SS1)
unnamed: C163.2, U35.17 (SS2)
unnamed: C168.1, L8.3, U35.12 (SWA2), U35.13 (SWB2)
unnamed: C158.1, R88.2, U35.5 (Vc1)
unnamed: C165.1, R97.2, U35.8 (Vc2)
unnamed: R83.2, U35.22 (~SHDN1)
unnamed: R98.2, U35.15 (~SHDN2)
P1_2P5V: C125.1, L1.2, TP1.1; also elsewhere on the board
P1_12P0V: R61.1; also elsewhere on the board
P1_VADJ: R5.1; also elsewhere on the board
P2_2P5V: C128.1, L2.2, TP2.1; also elsewhere on the board
P2_3P3V: R76.1; also elsewhere on the board
P2_12P0V: R65.1; also elsewhere on the board
P2_VADJ: R17.1; also elsewhere on the board
VDD3P3V: C152.1, L5.2, TP4.1; also elsewhere on the board

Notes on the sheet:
Vout = -((191k*83.3uA)-0.007V) =-15.90V
Vout = 0.8V*(1+(536k/100k)) =5.09V
Vout = (174k*83.3uA)+1.204V =15.7V
To Relay Coils
